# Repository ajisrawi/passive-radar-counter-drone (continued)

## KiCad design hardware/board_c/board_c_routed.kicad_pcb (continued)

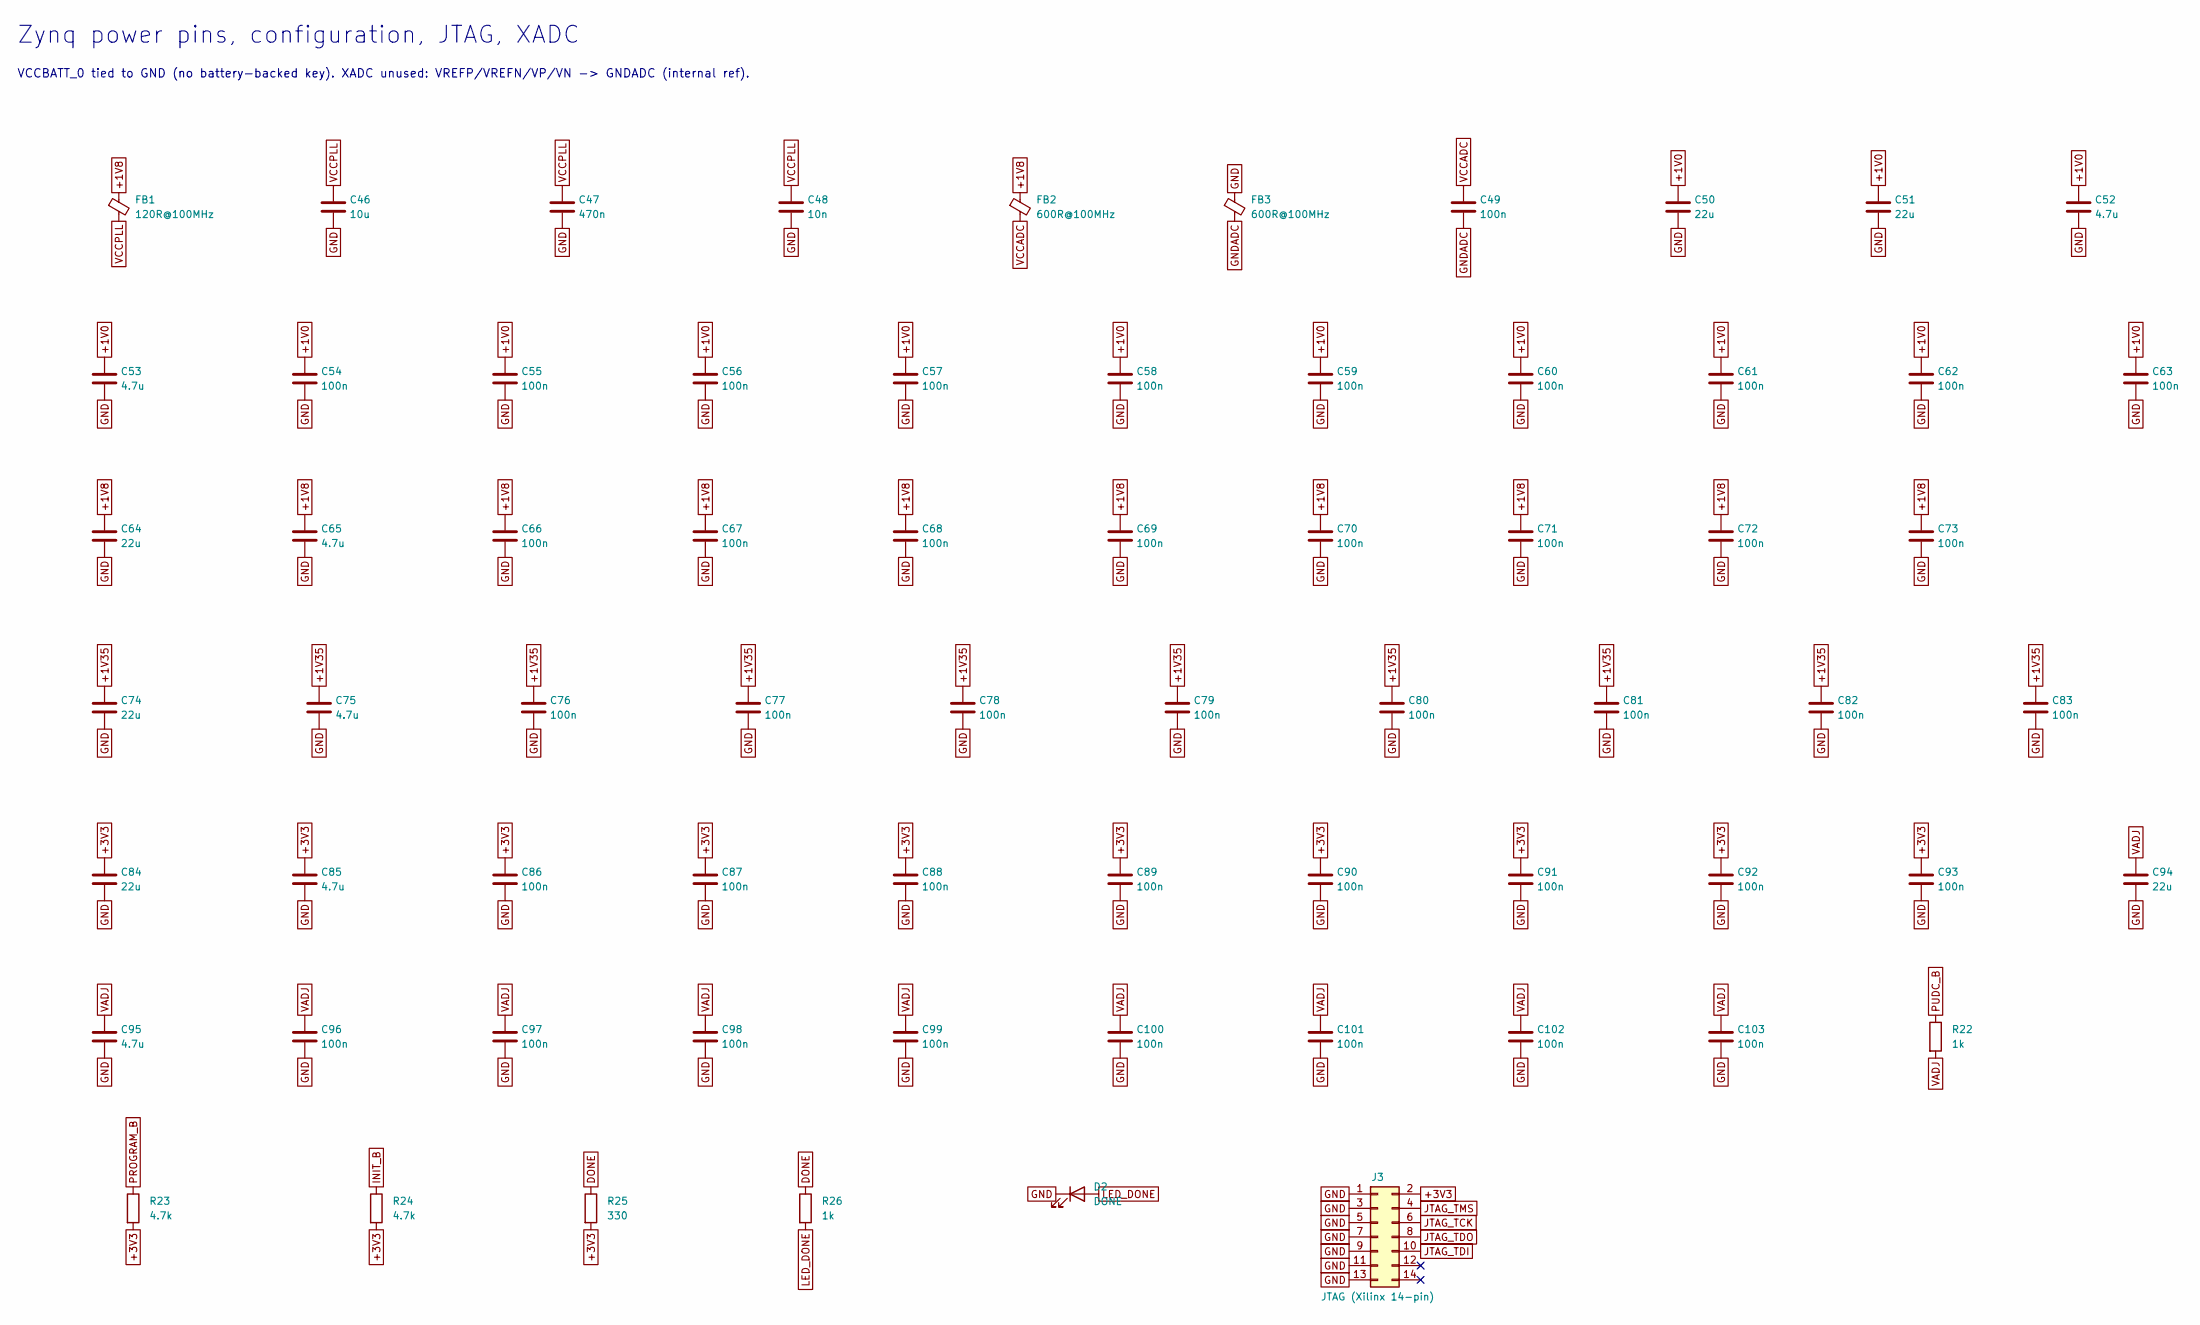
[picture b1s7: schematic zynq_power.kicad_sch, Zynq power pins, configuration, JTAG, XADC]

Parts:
C46: 10u; C_0603_1608Metric; LCSC C19702
C47: 470n; C_0402_1005Metric
C48: 10n; C_0402_1005Metric; LCSC C15195
C49, C54, C55, C56, C57, C58, C59, C60, C61, C62, C63, C66, C67, C68, C69, C70, C71, C72, C73, C76, C77, C78, C79, C80, C81, C82, C83, C86, C87, C88, C89, C90, C91, C92, C93, C96, C97, C98, C99, C100, C101, C102, C103: 100n; C_0402_1005Metric; LCSC C1525
C50, C51, C64, C74, C84, C94: 22u; C_0805_2012Metric; LCSC C45783
C52, C53, C65, C75, C85, C95: 4.7u; C_0603_1608Metric
D2: DONE; LED_0603_1608Metric
FB1: 120R@100MHz; L_0603_1608Metric
FB2, FB3: 600R@100MHz; L_0603_1608Metric
J3: JTAG (Xilinx 14-pin); PinHeader_2x07_P2.00mm_Vertical
R22, R26: 1k; R_0402_1005Metric; LCSC C11702
R23, R24: 4.7k; R_0402_1005Metric; LCSC C25900
R25: 330; R_0402_1005Metric

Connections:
+1V0: C50.1, C51.1, C52.1, C53.1, C54.1, C55.1, C56.1, C57.1, C58.1, C59.1, C60.1, C61.1, C62.1, C63.1; also elsewhere on the board
+1V8: C64.1, C65.1, C66.1, C67.1, C68.1, C69.1, C70.1, C71.1, C72.1, C73.1, FB1.1, FB2.1; also elsewhere on the board
+1V35: C74.1, C75.1, C76.1, C77.1, C78.1, C79.1, C80.1, C81.1, C82.1, C83.1; also elsewhere on the board
+3V3: C84.1, C85.1, C86.1, C87.1, C88.1, C89.1, C90.1, C91.1, C92.1, C93.1, J3.2, R23.2, R24.2, R25.2; also elsewhere on the board
DONE: R25.1, R26.1; also elsewhere on the board
GND: C46.2, C47.2, C48.2, C50.2, C51.2, C52.2, C53.2, C54.2, C55.2, C56.2, C57.2, C58.2, C59.2, C60.2, C61.2, C62.2, C63.2, C64.2, C65.2, C66.2, C67.2, C68.2, C69.2, C70.2, C71.2, C72.2, C73.2, C74.2, C75.2, C76.2, C77.2, C78.2, C79.2, C80.2, C81.2, C82.2, C83.2, C84.2, C85.2, C86.2, C87.2, C88.2, C89.2, C90.2, C91.2, C92.2, C93.2, C94.2, C95.2, C96.2, C97.2, C98.2, C99.2, C100.2, C101.2, C102.2, C103.2, D2.1 (K), FB3.1, J3.1, J3.3, J3.5, J3.7, J3.9, J3.11, J3.13; also elsewhere on the board
GNDADC: C49.2, FB3.2; also elsewhere on the board
INIT_B: R24.1; also elsewhere on the board
JTAG_TCK: J3.6; also elsewhere on the board
JTAG_TDI: J3.10; also elsewhere on the board
JTAG_TDO: J3.8; also elsewhere on the board
JTAG_TMS: J3.4; also elsewhere on the board
LED_DONE: D2.2 (A), R26.2
PROGRAM_B: R23.1; also elsewhere on the board
PUDC_B: R22.1; also elsewhere on the board
VADJ: C94.1, C95.1, C96.1, C97.1, C98.1, C99.1, C100.1, C101.1, C102.1, C103.1, R22.2; also elsewhere on the board
VCCADC: C49.1, FB2.2; also elsewhere on the board
VCCPLL: C46.1, C47.1, C48.1, FB1.2; also elsewhere on the board

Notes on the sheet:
Zynq power pins, configuration, JTAG, XADC
VCCBATT_0 tied to GND (no battery-backed key). XADC unused: VREFP/VREFN/VP/VN -> GNDADC (internal ref).

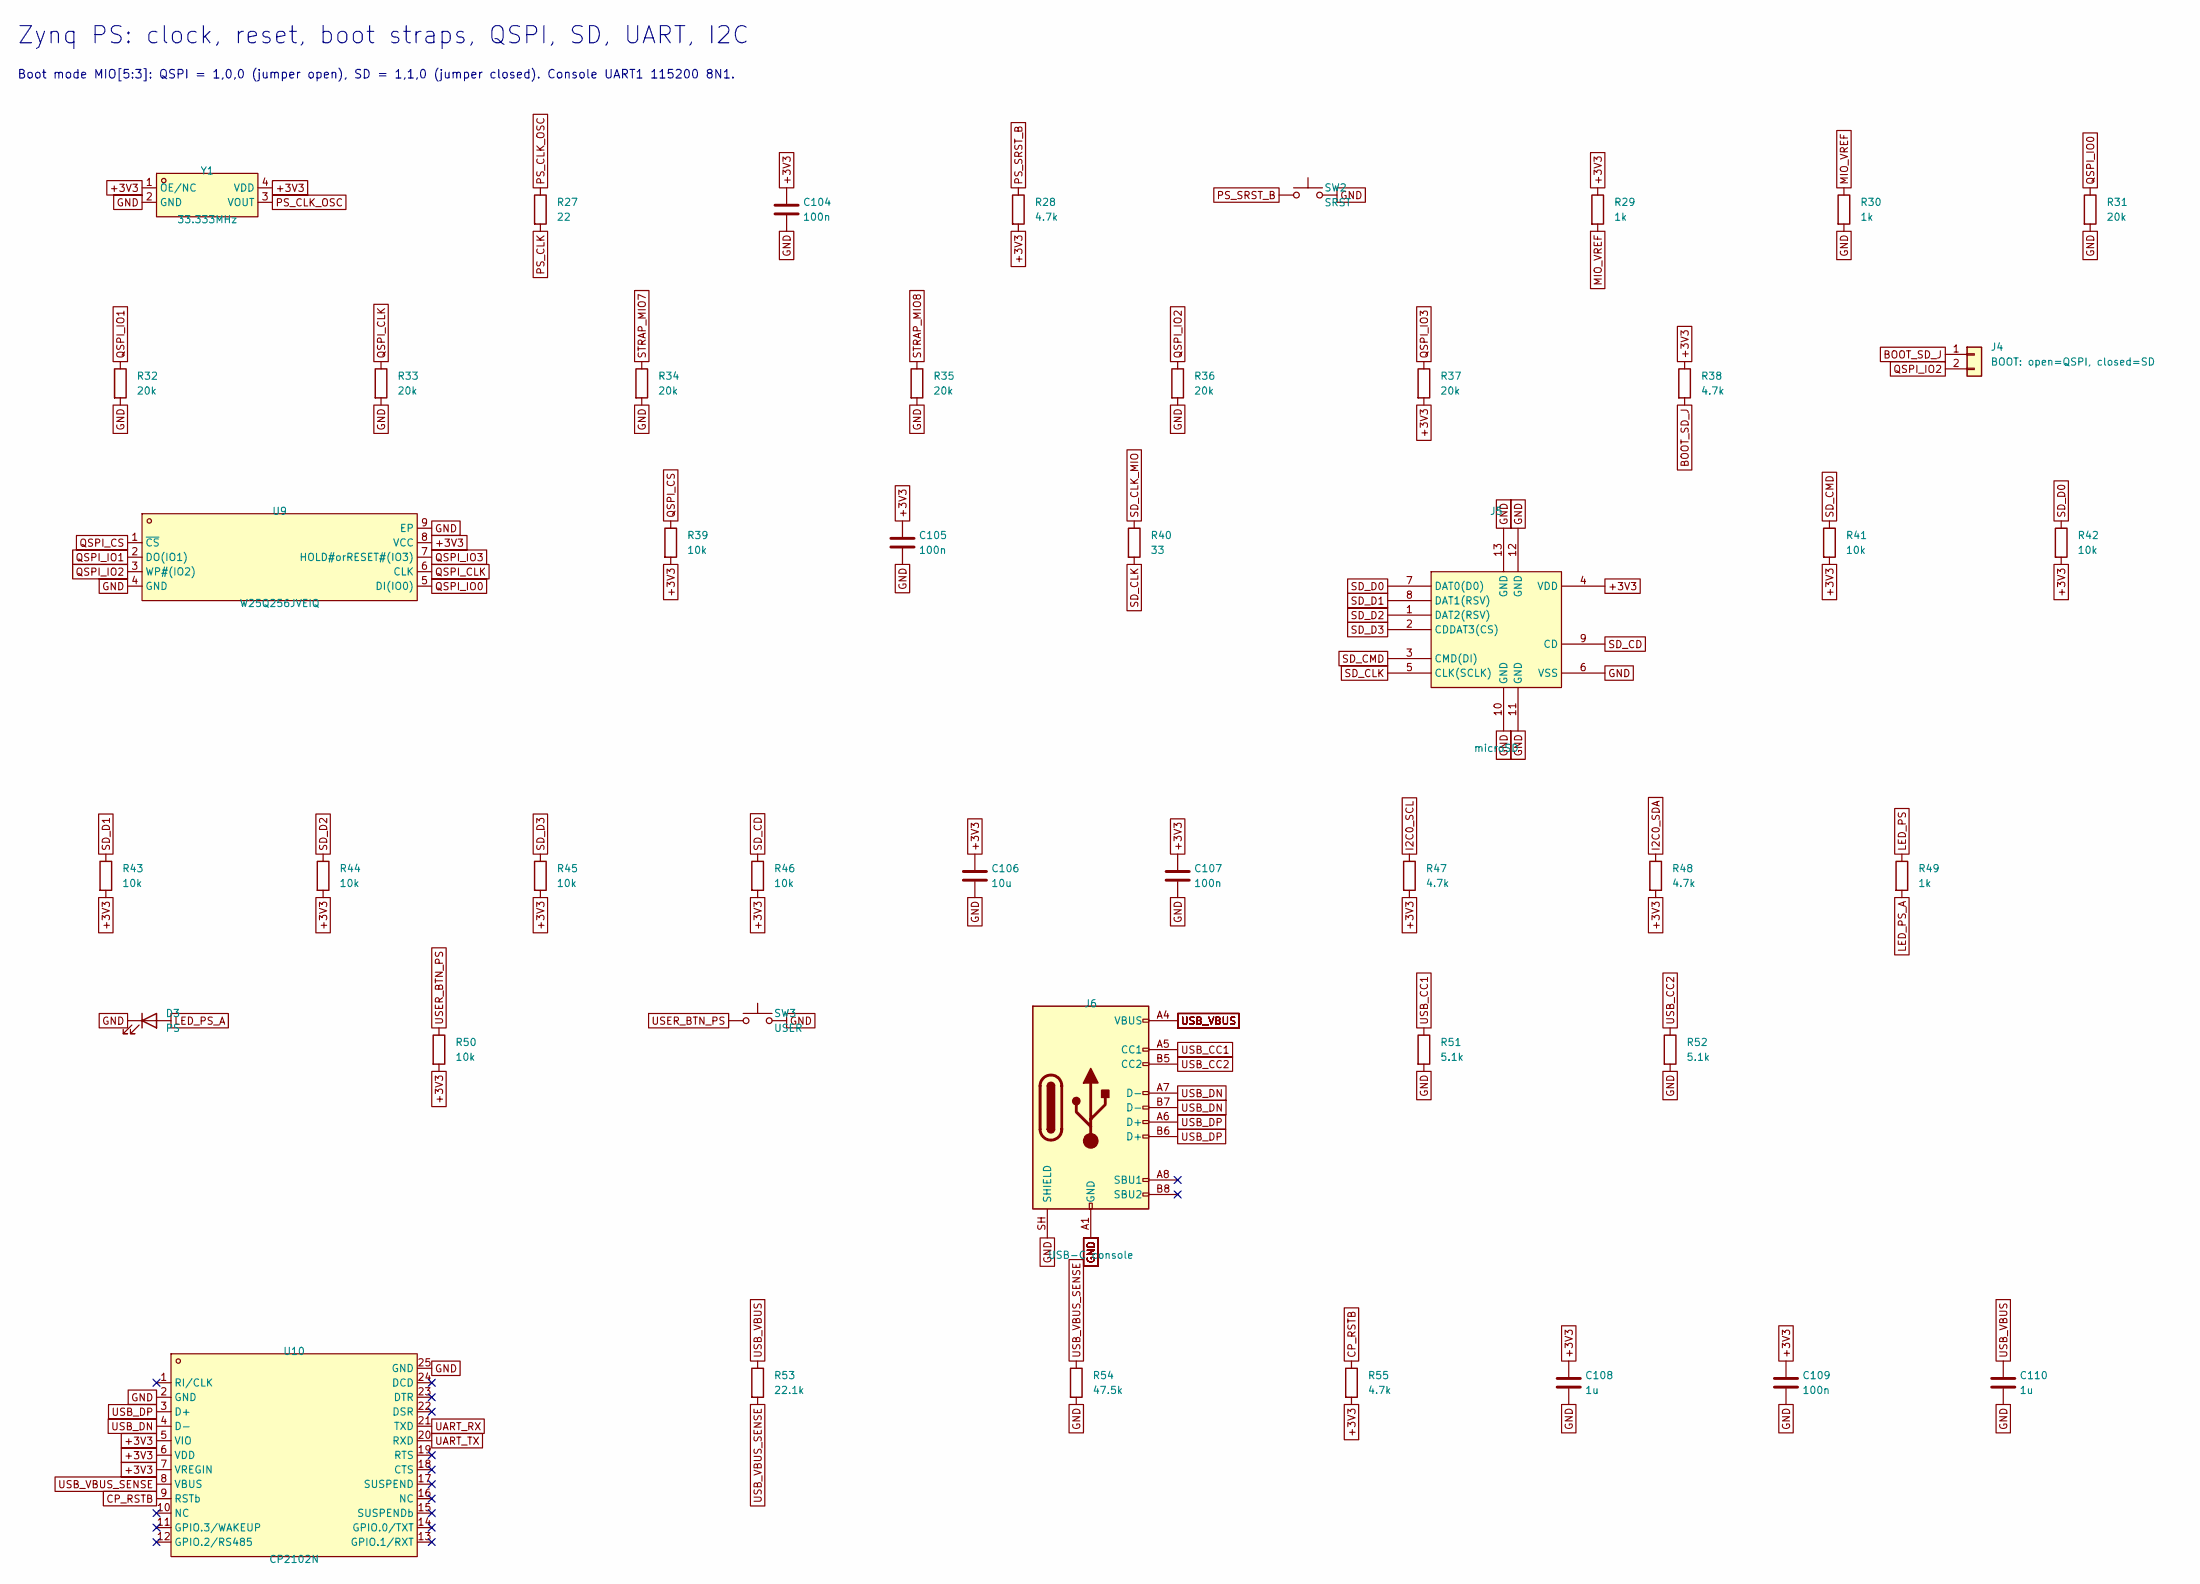
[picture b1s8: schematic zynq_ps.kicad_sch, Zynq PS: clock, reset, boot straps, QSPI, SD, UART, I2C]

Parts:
C104, C105, C107, C109: 100n; C_0402_1005Metric; LCSC C1525
C106: 10u; C_0603_1608Metric; LCSC C19702
C108, C110: 1u; C_0402_1005Metric; LCSC C52923
D3: PS; LED_0603_1608Metric
J4: BOOT: open=QSPI, closed=SD; PinHeader_1x02_P2.54mm_Vertical
J5: microSD; TF-SMD_TF-01A; MPN TF-01A; LCSC C91145
J6: USB-C console; USB_C_Receptacle_HRO_TYPE-C-31-M-12; LCSC C165948
R27: 22; R_0402_1005Metric
R28, R38, R47, R48, R55: 4.7k; R_0402_1005Metric; LCSC C25900
R29, R30, R49: 1k; R_0402_1005Metric; LCSC C11702
R31, R32, R33, R34, R35, R36, R37: 20k; R_0402_1005Metric
R39, R41, R42, R43, R44, R45, R46, R50: 10k; R_0402_1005Metric; LCSC C25744
R40: 33; R_0402_1005Metric
R51, R52: 5.1k; R_0402_1005Metric; LCSC C25905
R53: 22.1k; R_0402_1005Metric
R54: 47.5k; R_0402_1005Metric
SW2: SRST; SW_SPST_TL3342
SW3: USER; SW_SPST_TL3342
U9: W25Q256JVEIQ; WSON-8_L8.0-W6.10-P1.27-BL-EP; MPN W25Q256JVEIQ; LCSC C97522
U10: CP2102N; QFN-24_L4.0-W4.0-P0.50-TL-EP2.6; MPN CP2102N-A02-GQFN24R; LCSC C969151
Y1: 33.333MHz; OSC-SMD_4P-L5.0-W3.2-BL_OG8EL89CEI; MPN OG1EL89CEI-112YLC-33.333M; LCSC C5346412

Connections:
+3V3: C104.1, C105.1, C106.1, C107.1, C108.1, C109.1, J5.4 (VDD), R28.2, R29.1, R37.2, R38.1, R39.2, R41.2, R42.2, R43.2, R44.2, R45.2, R46.2, R47.2, R48.2, R50.2, R55.2, U9.8 (VCC), U10.5 (VIO), U10.6 (VDD), U10.7 (VREGIN), Y1.1 (OE/NC), Y1.4 (VDD); also elsewhere on the board
BOOT_SD_J: J4.1, R38.2
CP_RSTB: R55.1, U10.9 (RSTb)
GND: C104.2, C105.2, C106.2, C107.2, C108.2, C109.2, C110.2, D3.1 (K), J5.6 (VSS), J5.10 (GND), J5.11 (GND), J5.12 (GND), J5.13 (GND), J6.A1 (GND), J6.A12 (GND), J6.B1 (GND), J6.B12 (GND), J6.SH (SHIELD), R30.2, R31.2, R32.2, R33.2, R34.2, R35.2, R36.2, R51.2, R52.2, R54.2, SW2.2, SW3.2, U9.4 (GND), U9.9 (EP), U10.2 (GND), U10.25 (GND), Y1.2 (GND); also elsewhere on the board
I2C0_SCL: R47.1; also elsewhere on the board
I2C0_SDA: R48.1; also elsewhere on the board
LED_PS: R49.1; also elsewhere on the board
LED_PS_A: D3.2 (A), R49.2
MIO_VREF: R29.2, R30.1; also elsewhere on the board
PS_CLK: R27.2; also elsewhere on the board
PS_CLK_OSC: R27.1, Y1.3 (VOUT)
PS_SRST_B: R28.1, SW2.1; also elsewhere on the board
QSPI_CLK: R33.1, U9.6 (CLK); also elsewhere on the board
QSPI_CS: R39.1, U9.1 (~CS); also elsewhere on the board
QSPI_IO0: R31.1, U9.5 (DI(IO0)); also elsewhere on the board
QSPI_IO1: R32.1, U9.2 (DO(IO1)); also elsewhere on the board
QSPI_IO2: J4.2, R36.1, U9.3 (WP#(IO2)); also elsewhere on the board
QSPI_IO3: R37.1, U9.7 (HOLD#orRESET#(IO3)); also elsewhere on the board
SD_CD: J5.9 (CD), R46.1; also elsewhere on the board
SD_CLK: J5.5 (CLK(SCLK)), R40.2
SD_CLK_MIO: R40.1; also elsewhere on the board
SD_CMD: J5.3 (CMD(DI)), R41.1; also elsewhere on the board
SD_D0: J5.7 (DAT0(D0)), R42.1; also elsewhere on the board
SD_D1: J5.8 (DAT1(RSV)), R43.1; also elsewhere on the board
SD_D2: J5.1 (DAT2(RSV)), R44.1; also elsewhere on the board
SD_D3: J5.2 (CDDAT3(CS)), R45.1; also elsewhere on the board
STRAP_MIO7: R34.1; also elsewhere on the board
STRAP_MIO8: R35.1; also elsewhere on the board
UART_RX: U10.21 (TXD); also elsewhere on the board
UART_TX: U10.20 (RXD); also elsewhere on the board
USB_CC1: J6.A5 (CC1), R51.1
USB_CC2: J6.B5 (CC2), R52.1
USB_DN: J6.A7 (D-), J6.B7 (D-), U10.4 (D-)
USB_DP: J6.A6 (D+), J6.B6 (D+), U10.3 (D+)
USB_VBUS: C110.1, J6.A4 (VBUS), J6.A9 (VBUS), J6.B4 (VBUS), J6.B9 (VBUS), R53.1
USB_VBUS_SENSE: R53.2, R54.1, U10.8 (VBUS)
USER_BTN_PS: R50.1, SW3.1; also elsewhere on the board

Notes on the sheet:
Zynq PS: clock, reset, boot straps, QSPI, SD, UART, I2C
Boot mode MIO[5:3]: QSPI = 1,0,0 (jumper open), SD = 1,1,0 (jumper closed). Console UART1 115200 8N1.

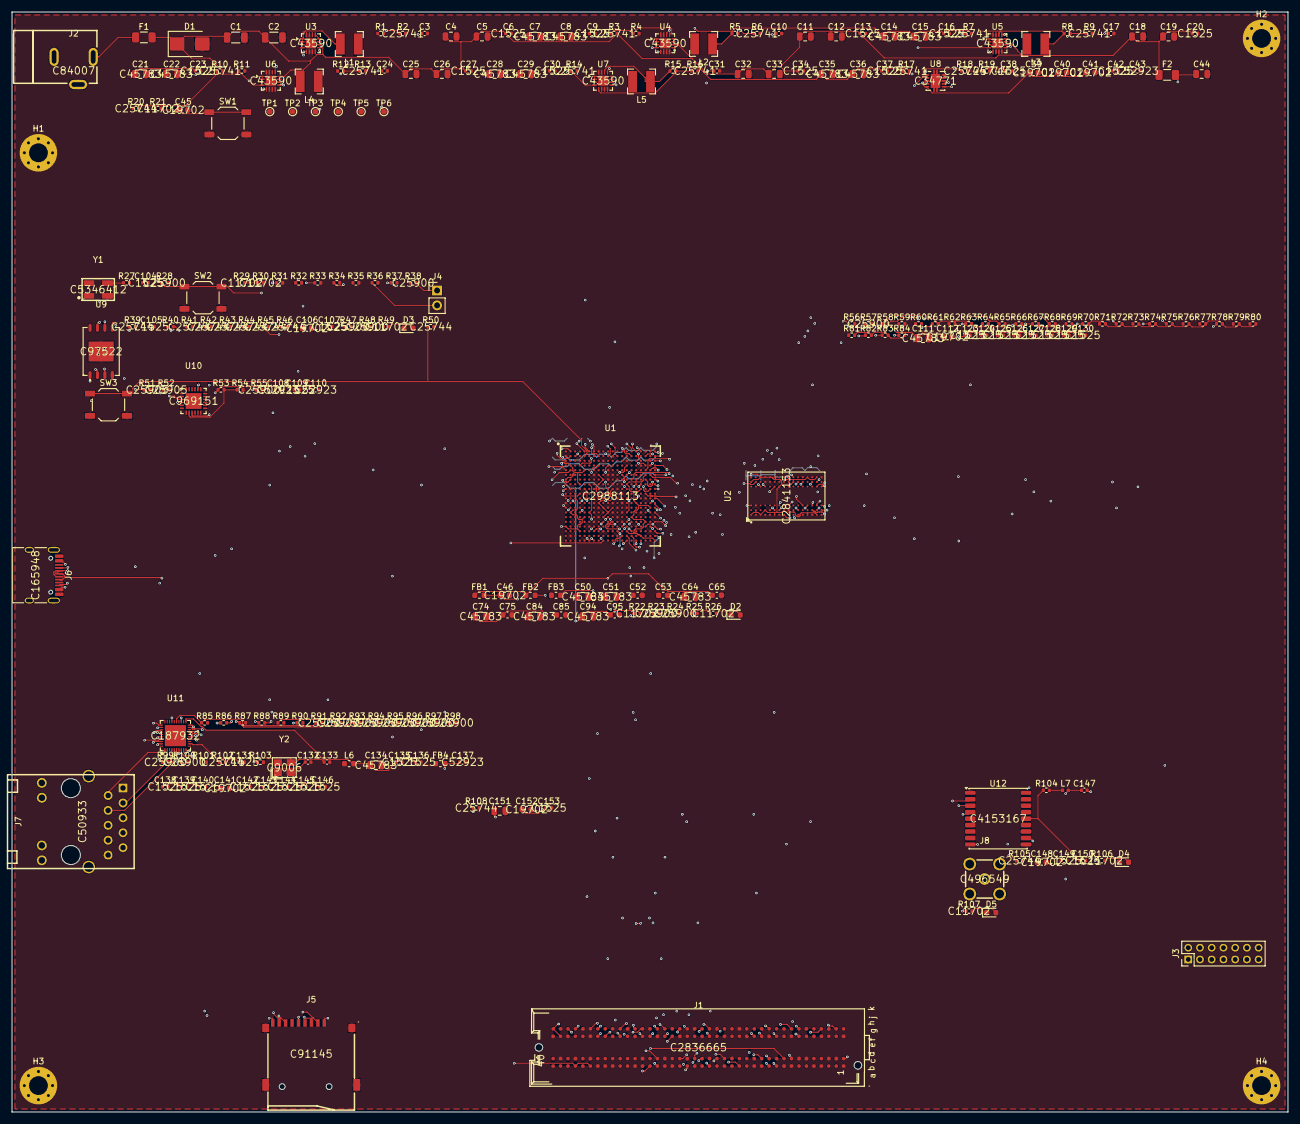
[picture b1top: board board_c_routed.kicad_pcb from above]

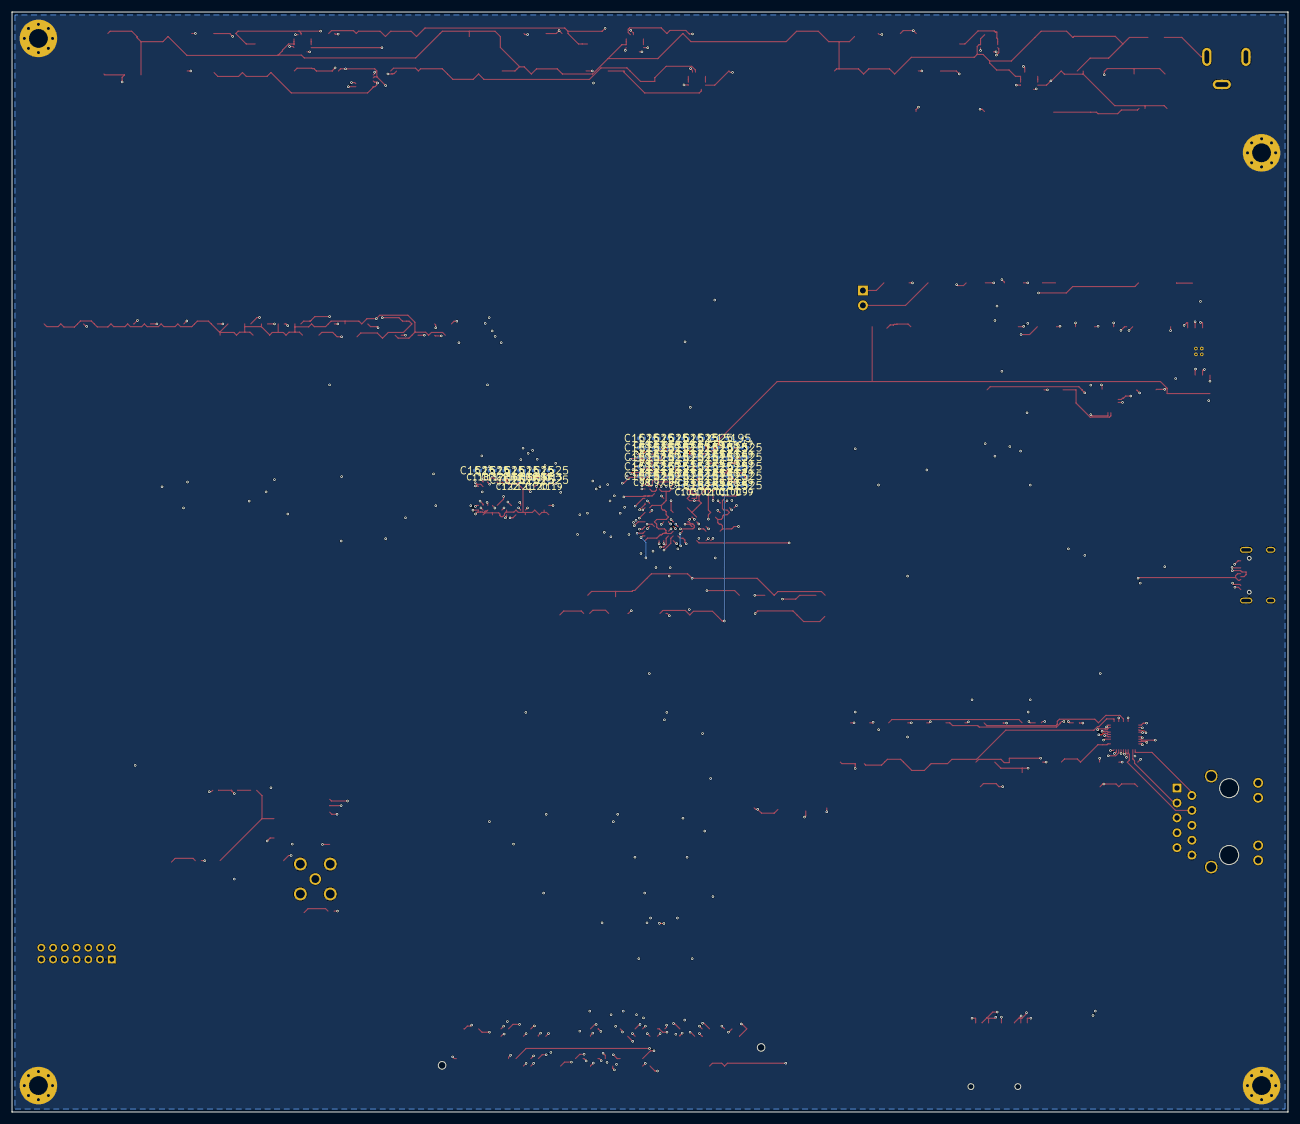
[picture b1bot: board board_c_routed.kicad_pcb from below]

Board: 8 copper layers, 217.5 x 187.5 mm, 314 parts (55 on the bottom side), 251 nets.

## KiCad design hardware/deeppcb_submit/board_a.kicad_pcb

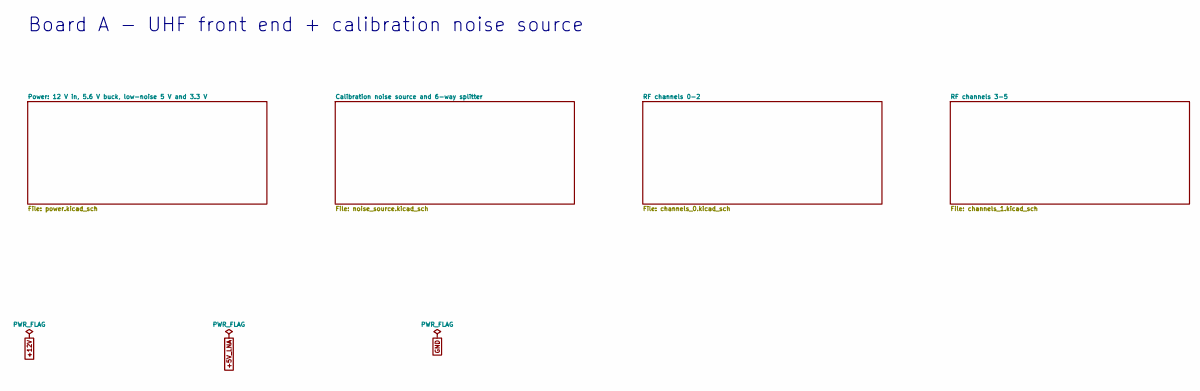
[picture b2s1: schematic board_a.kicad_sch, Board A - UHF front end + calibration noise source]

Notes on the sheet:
Board A - UHF front end + calibration noise source

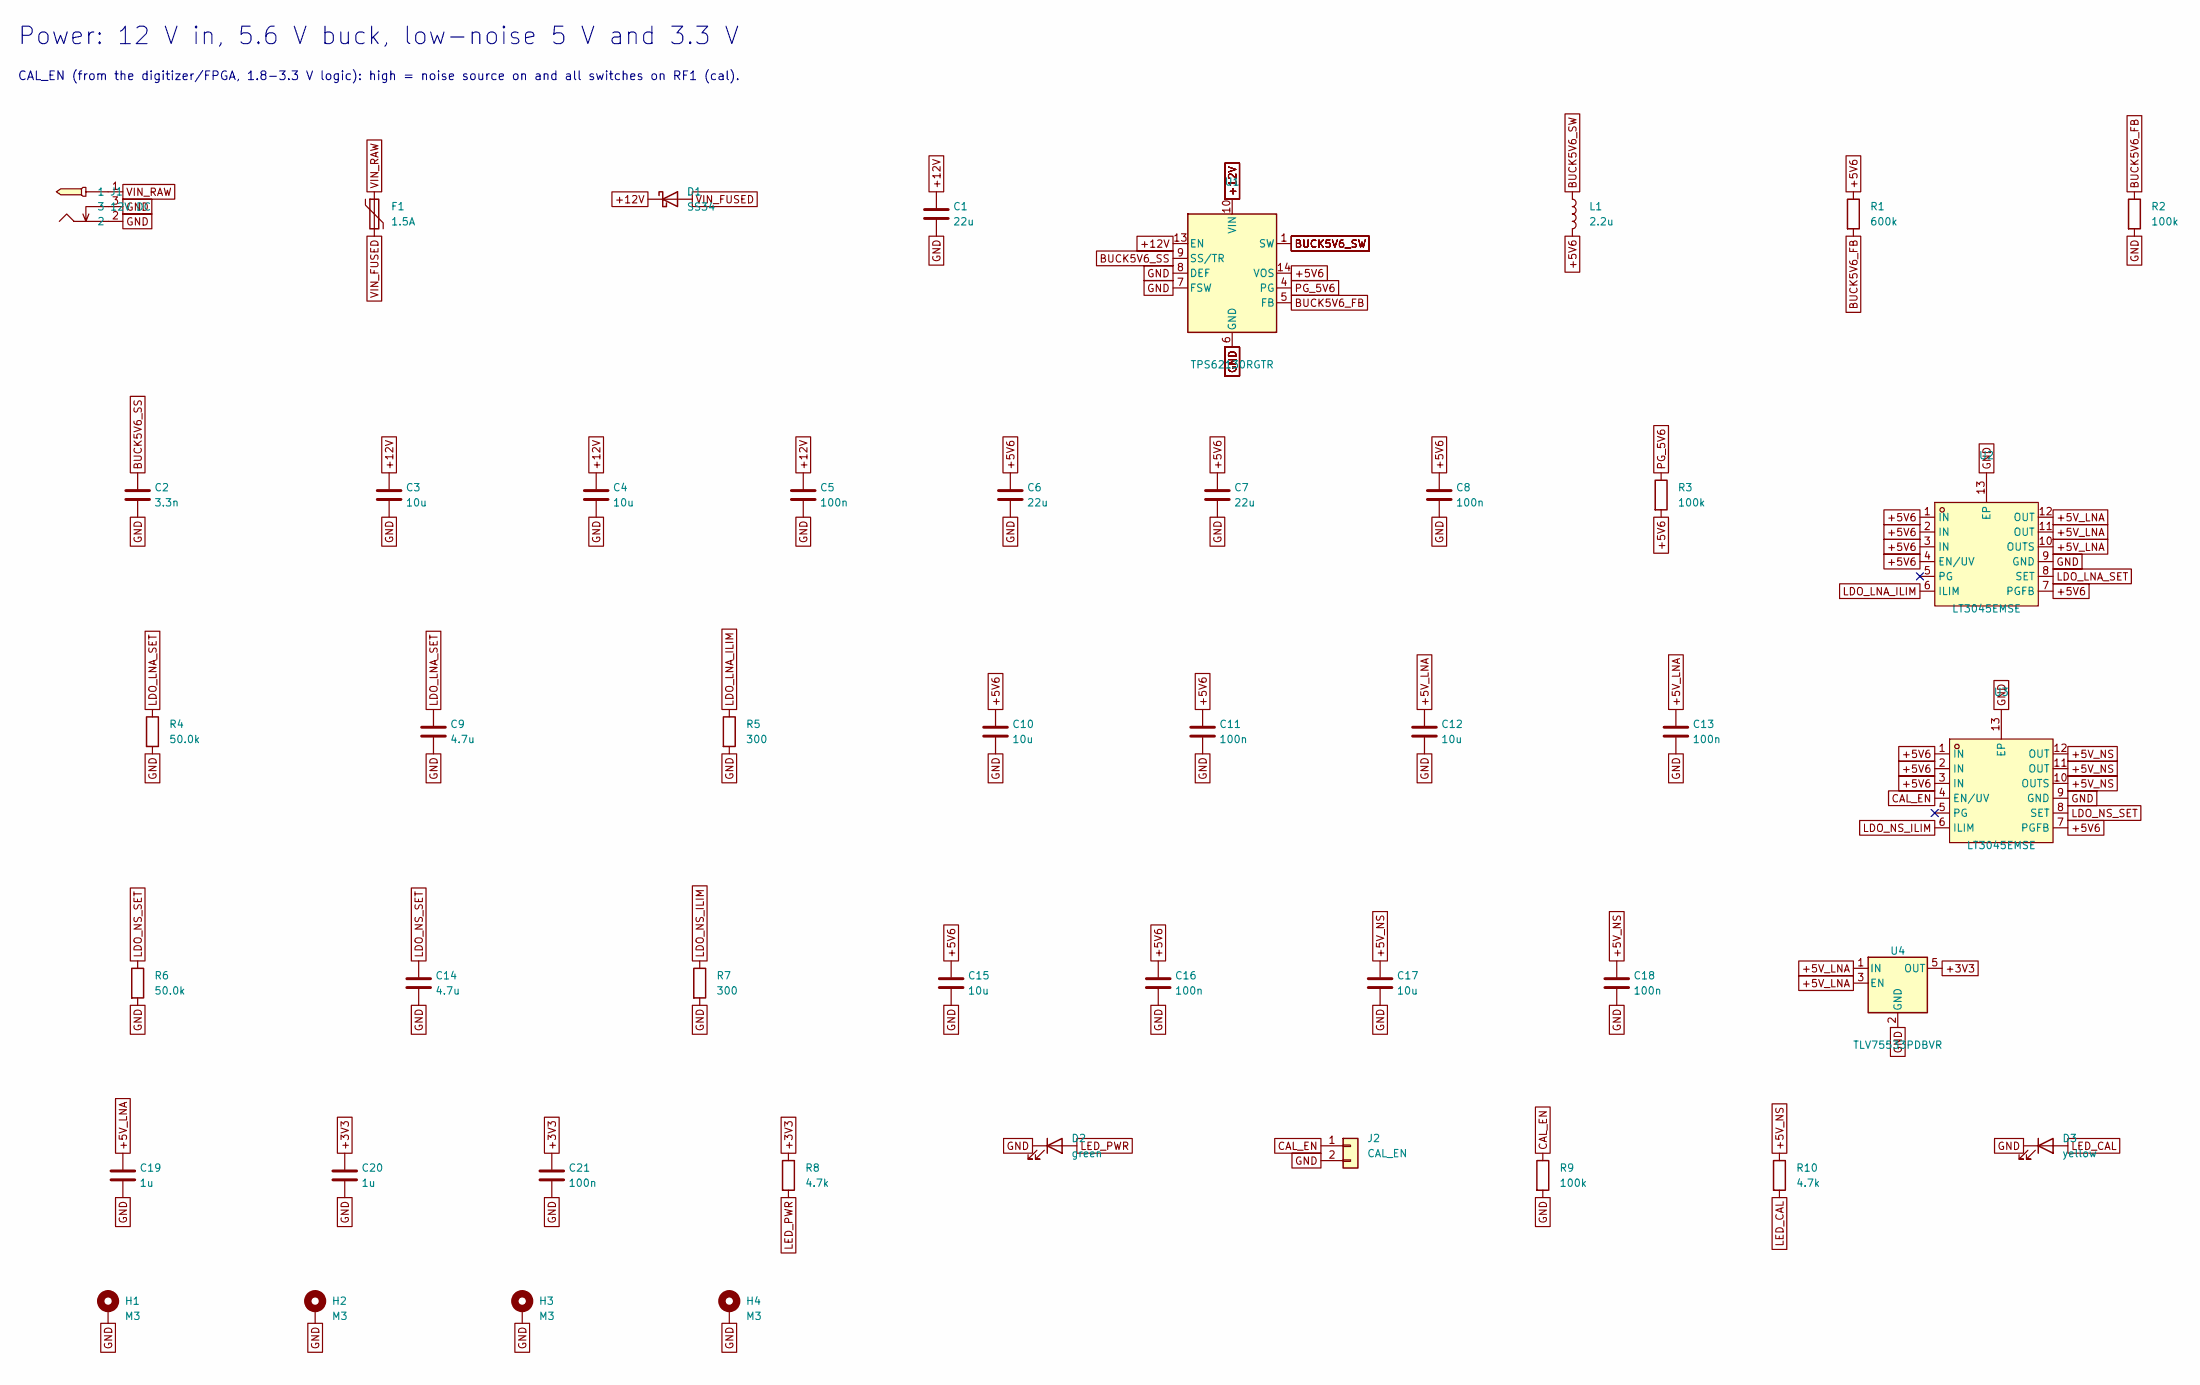
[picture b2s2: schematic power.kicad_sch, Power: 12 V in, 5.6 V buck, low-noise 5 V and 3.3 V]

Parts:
C1: 22u; C_1206_3216Metric
C2: 3.3n; C_0402_1005Metric
C3, C4: 10u; C_0805_2012Metric
C5, C8, C11, C13, C16, C18, C21: 100n; C_0402_1005Metric; LCSC C1525
C6, C7: 22u; C_0805_2012Metric; LCSC C45783
C9, C14: 4.7u; C_0603_1608Metric
C10, C12, C15, C17: 10u; C_0603_1608Metric; LCSC C19702
C19, C20: 1u; C_0402_1005Metric; LCSC C52923
D1: SS34; D_SMA; MPN SS34; LCSC C8678
D2: green; LED_0603_1608Metric
D3: yellow; LED_0603_1608Metric
F1: 1.5A; Fuse_1206_3216Metric
H1, H2, H3, H4: M3; MountingHole_3.2mm_M3_Pad_Via
J1: 12V DC; DC-IN-TH_DC-005C-20A; MPN DC-005C-20A; LCSC C84007
J2: CAL_EN; PinHeader_1x02_P2.54mm_Vertical
L1: 2.2u; L_Bourns-SRN4018; MPN SRN4018-2R2M
R1: 600k; R_0402_1005Metric
R2, R3, R9: 100k; R_0402_1005Metric; LCSC C25741
R4, R6: 50.0k; R_0402_1005Metric; Tolerance 0.1%
R5, R7: 300; R_0402_1005Metric
R8, R10: 4.7k; R_0402_1005Metric; LCSC C25900
U1: TPS62130RGTR; VQFN-16-1EP_3x3mm_P0.5mm_EP1.68x1.68mm; MPN TPS62130RGTR; LCSC C43590
U2, U3: LT3045EMSE; MSOP-12_L4.0-W3.0-P0.65-LS4.9-BL-EP; MPN LT3045EMSE#PBF; LCSC C580012
U4: TLV75533PDBVR; SOT-23-5; LCSC C404027

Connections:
+3V3: C20.1, C21.1, R8.1, U4.5 (OUT); also elsewhere on the board
+5V6: C6.1, C7.1, C8.1, C10.1, C11.1, C15.1, C16.1, L1.2, R1.1, R3.2, U1.14 (VOS), U2.1 (IN), U2.2 (IN), U2.3 (IN), U2.4 (EN/UV), U2.7 (PGFB), U3.1 (IN), U3.2 (IN), U3.3 (IN), U3.7 (PGFB)
+5V_LNA: C12.1, C13.1, C19.1, U2.10 (OUTS), U2.11 (OUT), U2.12 (OUT), U4.1 (IN), U4.3 (EN); also elsewhere on the board
+5V_NS: C17.1, C18.1, R10.1, U3.10 (OUTS), U3.11 (OUT), U3.12 (OUT); also elsewhere on the board
+12V: C1.1, C3.1, C4.1, C5.1, D1.1 (K), U1.10 (VIN), U1.11 (VIN), U1.12 (VIN), U1.13 (EN)
BUCK5V6_FB: R1.2, R2.1, U1.5 (FB)
BUCK5V6_SS: C2.1, U1.9 (SS/TR)
BUCK5V6_SW: L1.1, U1.1 (SW), U1.2 (SW), U1.3 (SW)
CAL_EN: J2.1, R9.1, U3.4 (EN/UV); also elsewhere on the board
GND: C1.2, C2.2, C3.2, C4.2, C5.2, C6.2, C7.2, C8.2, C9.2, C10.2, C11.2, C12.2, C13.2, C14.2, C15.2, C16.2, C17.2, C18.2, C19.2, C20.2, C21.2, D2.1 (K), D3.1 (K), H1.1, H2.1, H3.1, H4.1, J1.2, J1.3, J2.2, R2.2, R4.2, R5.2, R6.2, R7.2, R9.2, U1.6 (GND), U1.7 (FSW), U1.8 (DEF), U1.15 (GND), U1.16 (GND), U1.17 (GND), U2.9 (GND), U2.13 (EP), U3.9 (GND), U3.13 (EP), U4.2 (GND); also elsewhere on the board
LDO_LNA_ILIM: R5.1, U2.6 (ILIM)
LDO_LNA_SET: C9.1, R4.1, U2.8 (SET)
LDO_NS_ILIM: R7.1, U3.6 (ILIM)
LDO_NS_SET: C14.1, R6.1, U3.8 (SET)
LED_CAL: D3.2 (A), R10.2
LED_PWR: D2.2 (A), R8.2
PG_5V6: R3.1, U1.4 (PG)
VIN_FUSED: D1.2 (A), F1.2
VIN_RAW: F1.1, J1.1

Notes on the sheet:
Power: 12 V in, 5.6 V buck, low-noise 5 V and 3.3 V
CAL_EN (from the digitizer/FPGA, 1.8-3.3 V logic): high = noise source on and all switches on RF1 (cal).

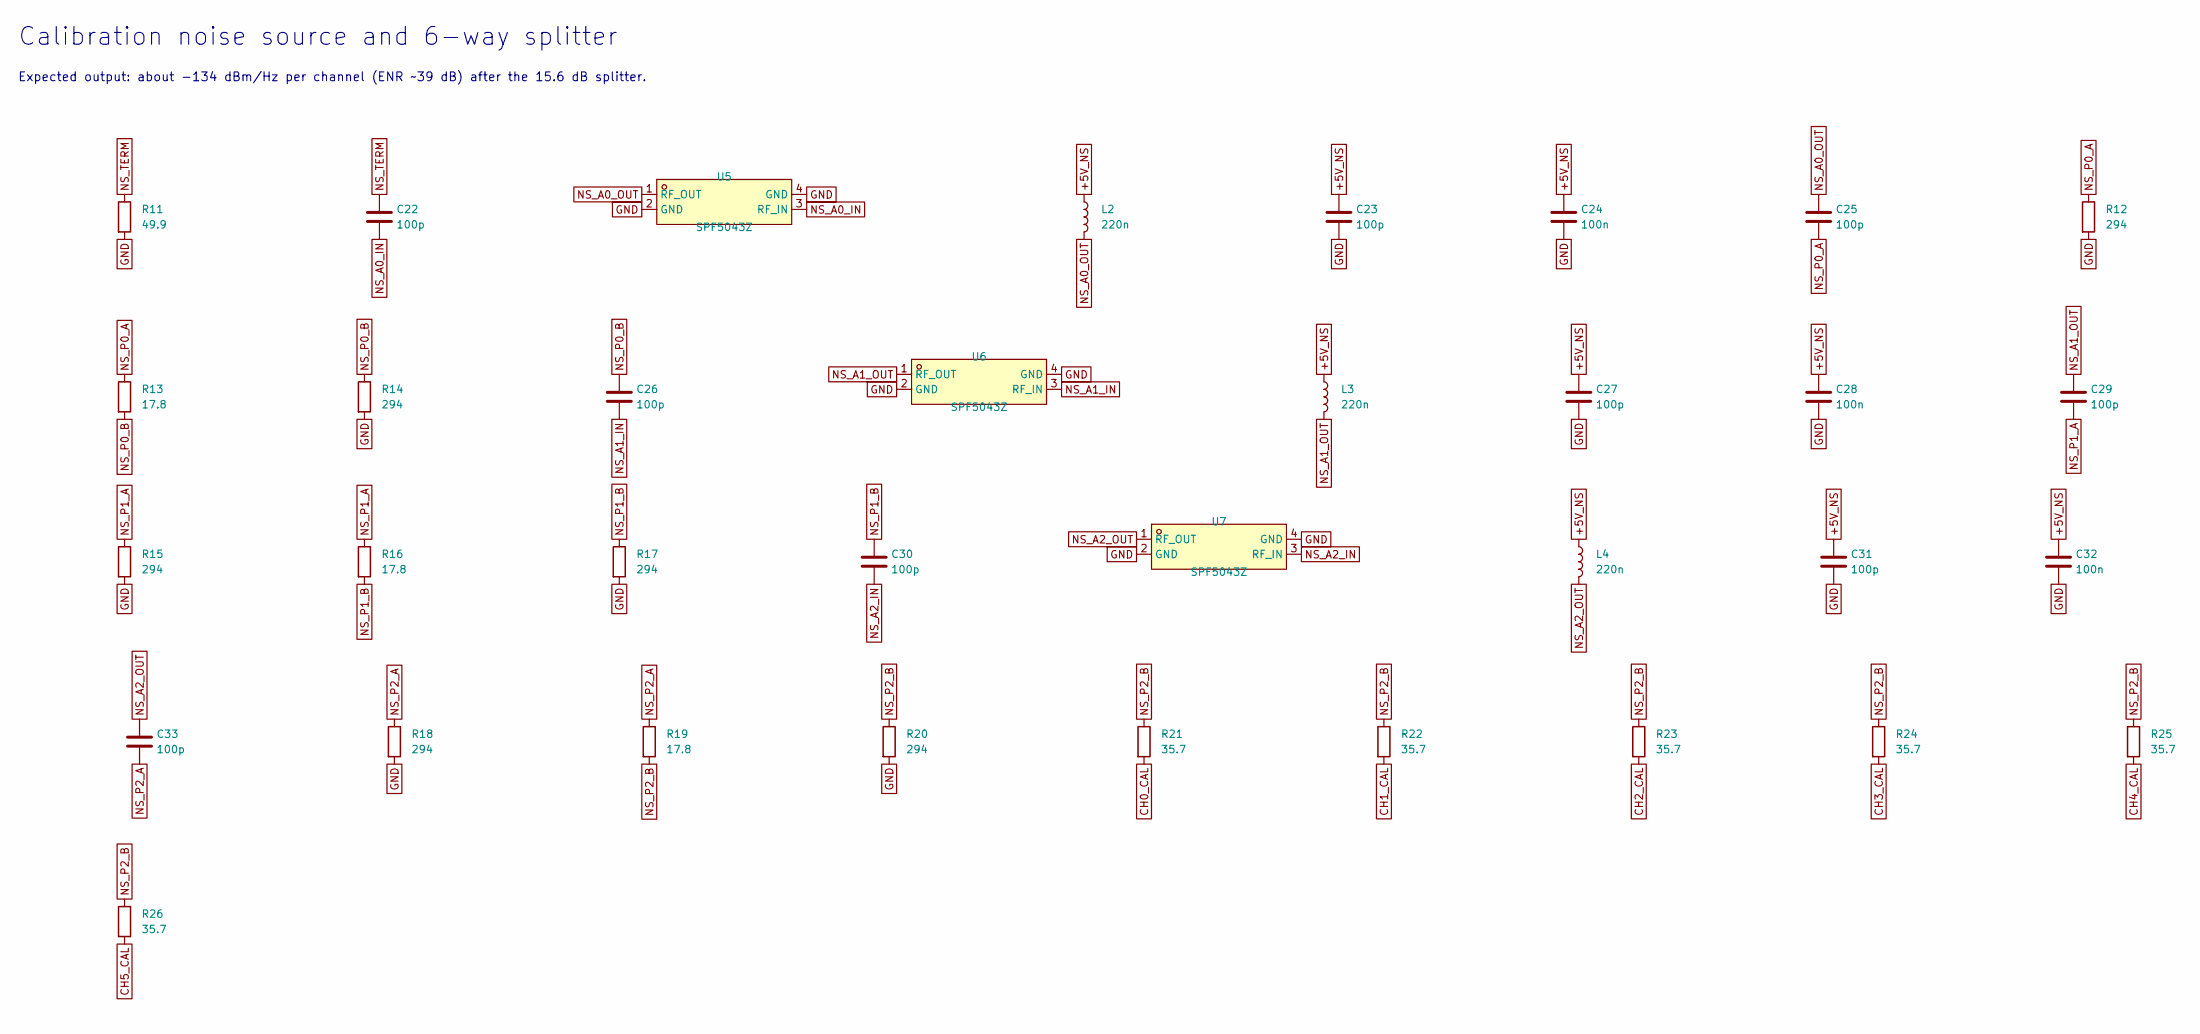
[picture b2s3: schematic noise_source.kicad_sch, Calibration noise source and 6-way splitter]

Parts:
C22, C23, C25, C26, C27, C29, C30, C31, C33: 100p; C_0402_1005Metric
C24, C28, C32: 100n; C_0402_1005Metric; LCSC C1525
L2, L3, L4: 220n; L_0603_1608Metric
R11: 49.9; R_0402_1005Metric
R12, R14, R15, R17, R18, R20: 294; R_0402_1005Metric
R13, R16, R19: 17.8; R_0402_1005Metric
R21, R22, R23, R24, R25, R26: 35.7; R_0402_1005Metric
U5, U6, U7: SPF5043Z; SOT343_L2.0-W1.3-P1.30-LS2.1-BL; MPN SPF5043Z; LCSC C470902

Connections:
+5V_NS: C23.1, C24.1, C27.1, C28.1, C31.1, C32.1, L2.1, L3.1, L4.1; also elsewhere on the board
CH0_CAL: R21.2; also elsewhere on the board
CH1_CAL: R22.2; also elsewhere on the board
CH2_CAL: R23.2; also elsewhere on the board
CH3_CAL: R24.2; also elsewhere on the board
CH4_CAL: R25.2; also elsewhere on the board
CH5_CAL: R26.2; also elsewhere on the board
GND: C23.2, C24.2, C27.2, C28.2, C31.2, C32.2, R11.2, R12.2, R14.2, R15.2, R17.2, R18.2, R20.2, U5.2 (GND), U5.4 (GND), U6.2 (GND), U6.4 (GND), U7.2 (GND), U7.4 (GND); also elsewhere on the board
NS_A0_IN: C22.2, U5.3 (RF_IN)
NS_A0_OUT: C25.1, L2.2, U5.1 (RF_OUT)
NS_A1_IN: C26.2, U6.3 (RF_IN)
NS_A1_OUT: C29.1, L3.2, U6.1 (RF_OUT)
NS_A2_IN: C30.2, U7.3 (RF_IN)
NS_A2_OUT: C33.1, L4.2, U7.1 (RF_OUT)
NS_P0_A: C25.2, R12.1, R13.1
NS_P0_B: C26.1, R13.2, R14.1
NS_P1_A: C29.2, R15.1, R16.1
NS_P1_B: C30.1, R16.2, R17.1
NS_P2_A: C33.2, R18.1, R19.1
NS_P2_B: R19.2, R20.1, R21.1, R22.1, R23.1, R24.1, R25.1, R26.1
NS_TERM: C22.1, R11.1

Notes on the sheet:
Calibration noise source and 6-way splitter
Expected output: about -134 dBm/Hz per channel (ENR ~39 dB) after the 15.6 dB splitter.
